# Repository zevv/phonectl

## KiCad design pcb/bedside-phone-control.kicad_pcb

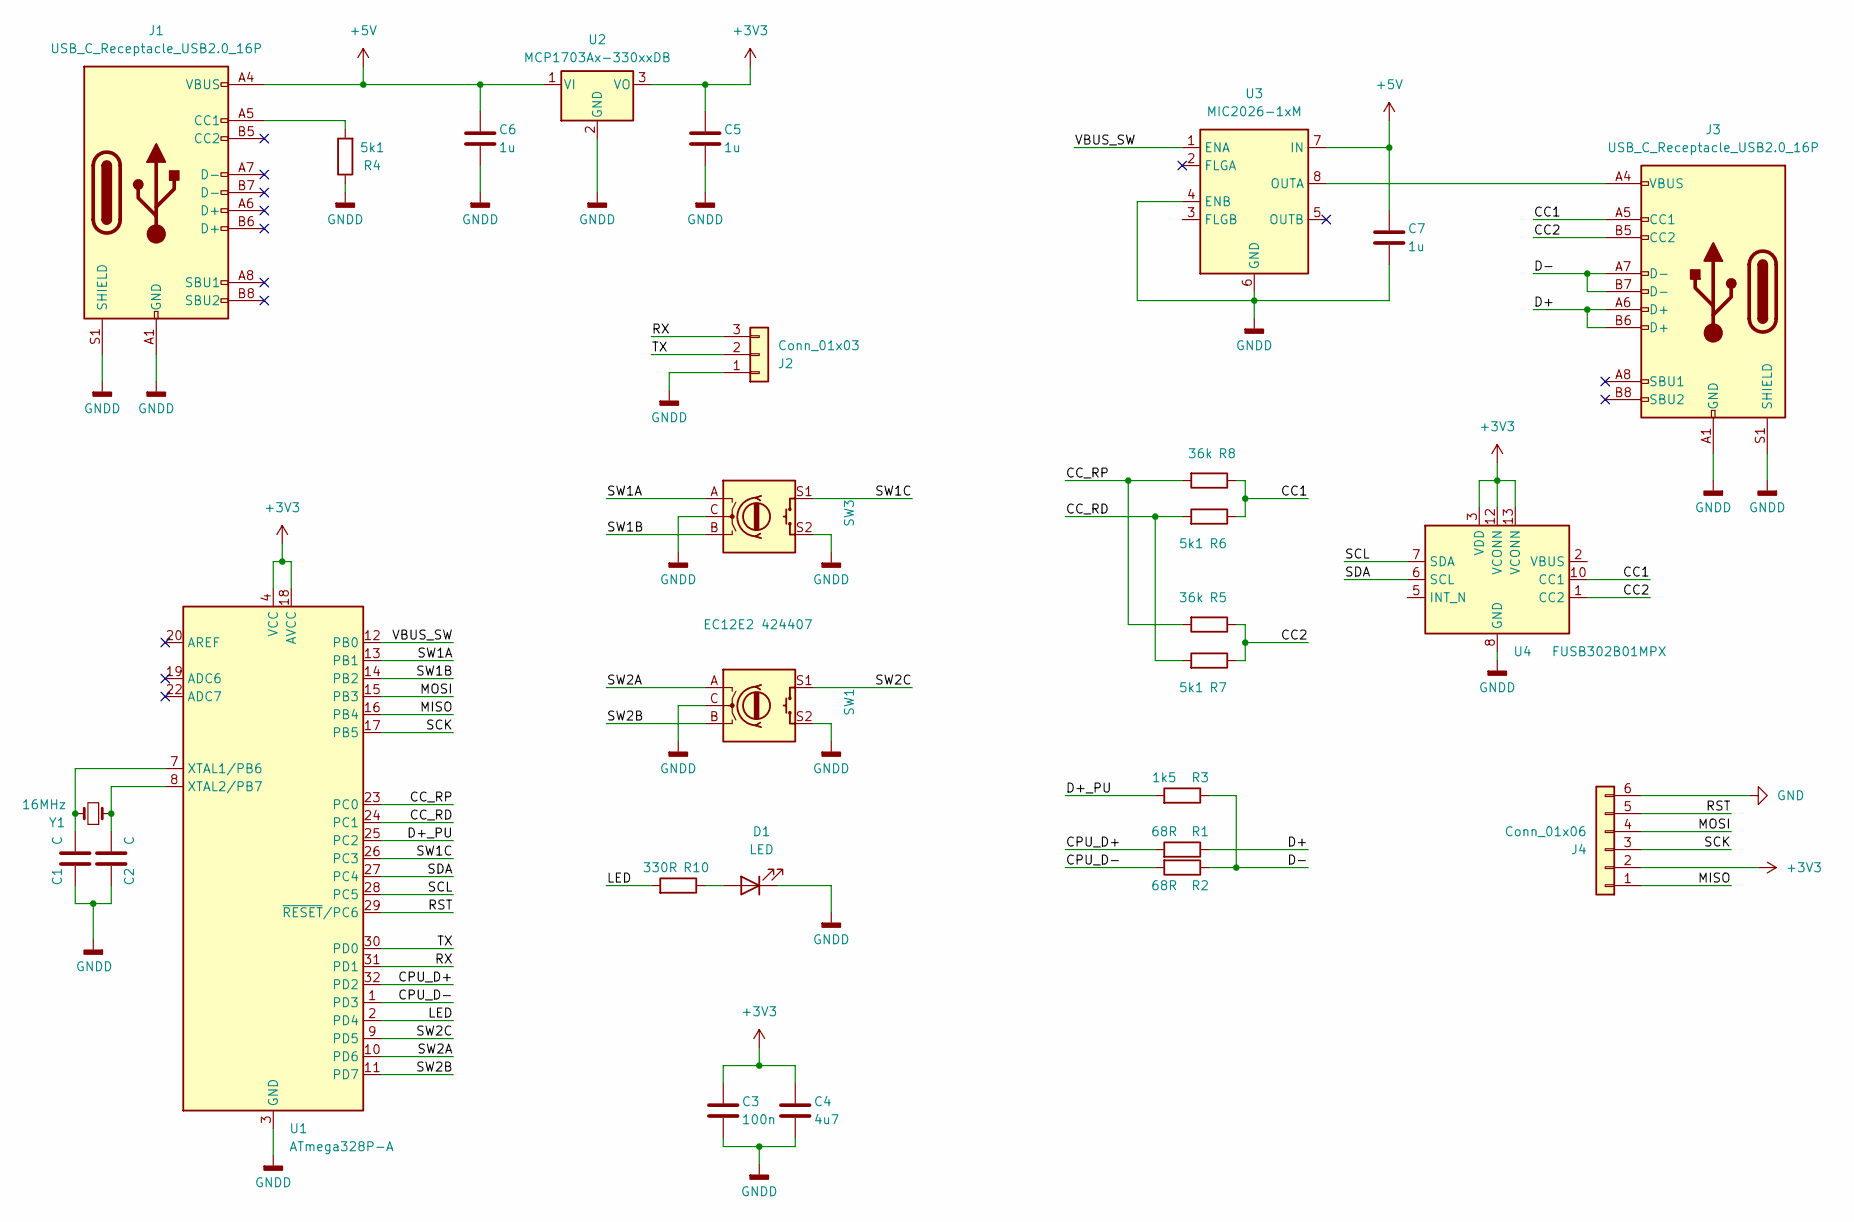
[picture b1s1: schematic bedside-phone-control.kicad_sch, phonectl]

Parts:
C1, C2: C; C_0603_1608Metric
C3: 100n; C_0603_1608Metric
C4: 4u7; C_0603_1608Metric
C5, C6, C7: 1u; C_0603_1608Metric
D1: LED; LED_D3.0mm
J1, J3: USB_C_Receptacle_USB2.0_16P; USB_C_Receptacle_Molex_105450-0101
J2: Conn_01x03; PinHeader_1x03_P2.54mm_Vertical
J4: Conn_01x06; PinHeader_2x03_P2.54mm_Vertical
R1, R2: 68R; R_0603_1608Metric
R3: 1k5; R_0603_1608Metric
R4, R6, R7: 5k1; R_0603_1608Metric
R5, R8: 36k; R_0603_1608Metric
R10: 330R; R_0603_1608Metric
SW1: RotaryEncoder_Switch; RotaryEncoder_Alps_EC11E-Switch_Vertical_H20mm
SW3: EC12E2 424407; RotaryEncoder_Alps_EC11E-Switch_Vertical_H20mm
U1: ATmega328P-A; TQFP-32_7x7mm_P0.8mm
U2: MCP1703Ax-330xxDB; SOT-223-3_TabPin2
U3: MIC2026-1xM; SOIC-8_3.9x4.9mm_P1.27mm
U4: FUSB302B01MPX; WQFN-14-1EP_2.5x2.5mm_P0.5mm_EP1.45x1.45mm
Y1: 16MHz; Crystal_SMD_Abracon_ABM3-2Pin_5.0x3.2mm_HandSoldering

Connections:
+3V3: C3.2, C4.2, C5.2, J4.2, U1.4 (VCC), U1.6 (VCC), U1.18 (AVCC), U2.3 (VO), U4.3 (VDD), U4.4 (VDD), U4.12 (VCONN), U4.13 (VCONN)
+5V: C6.2, C7.2, J1.A4 (VBUS), J1.A9 (VBUS), J1.B4 (VBUS), J1.B9 (VBUS), U2.1 (VI), U3.7 (IN)
/CC1: J3.A5 (CC1), R6.1, R8.1, U4.10 (CC1), U4.11 (CC1)
/CC2: J3.B5 (CC2), R5.1, R7.1, U4.1 (CC2), U4.14 (CC2)
/CC_RD: R6.2, R7.2, U1.24 (PC1)
/CC_RP: R5.2, R8.2, U1.23 (PC0)
/CPU_D+: R1.2, U1.32 (PD2)
/CPU_D-: R2.2, U1.1 (PD3)
/D+: J3.A6 (D+), J3.B6 (D+), R1.1
/D+_PU: R3.2, U1.25 (PC2)
/D-: J3.A7 (D-), J3.B7 (D-), R2.1, R3.1
/LED: R10.2, U1.2 (PD4)
/MISO: J4.1, U1.16 (PB4)
/MOSI: J4.4, U1.15 (PB3)
/RST: J4.5, U1.29 (~RESET/PC6)
/RX: J2.3, U1.31 (PD1)
/SCK: J4.3, U1.17 (PB5)
/SCL: U1.28 (PC5), U4.7 (SDA)
/SDA: U1.27 (PC4), U4.6 (SCL)
/SW1A: SW3.A, U1.13 (PB1)
/SW1B: SW3.B, U1.14 (PB2)
/SW1C: SW3.S1, U1.26 (PC3)
/SW2A: SW1.A, U1.10 (PD6)
/SW2B: SW1.B, U1.11 (PD7)
/SW2C: SW1.S1, U1.9 (PD5)
/TX: J2.2, U1.30 (PD0)
/VBUS_SW: U1.12 (PB0), U3.1 (ENA)
GND: J4.6
GNDD: C1.2, C2.2, C3.1, C4.1, C5.1, C6.1, C7.1, D1.1 (K), J1.A1 (GND), J1.A12 (GND), J1.B1 (GND), J1.B12 (GND), J1.S1 (SHIELD), J2.1, J3.A1 (GND), J3.A12 (GND), J3.B1 (GND), J3.B12 (GND), J3.S1 (SHIELD), R4.1, SW1.C, SW1.S2, SW3.C, SW3.S2, U1.3 (GND), U1.5 (GND), U1.21 (GND), U2.2 (GND), U3.4 (ENB), U3.6 (GND), U4.8 (GND), U4.9 (GND), U4.15 (GND)
unnamed: D1.2 (A), R10.1
unnamed: J1.A5 (CC1), R4.2
unnamed: C1.1, U1.7 (XTAL1/PB6), Y1.2
unnamed: C2.1, U1.8 (XTAL2/PB7), Y1.1
unnamed: J3.A4 (VBUS), J3.A9 (VBUS), J3.B4 (VBUS), J3.B9 (VBUS), U3.8 (OUTA)

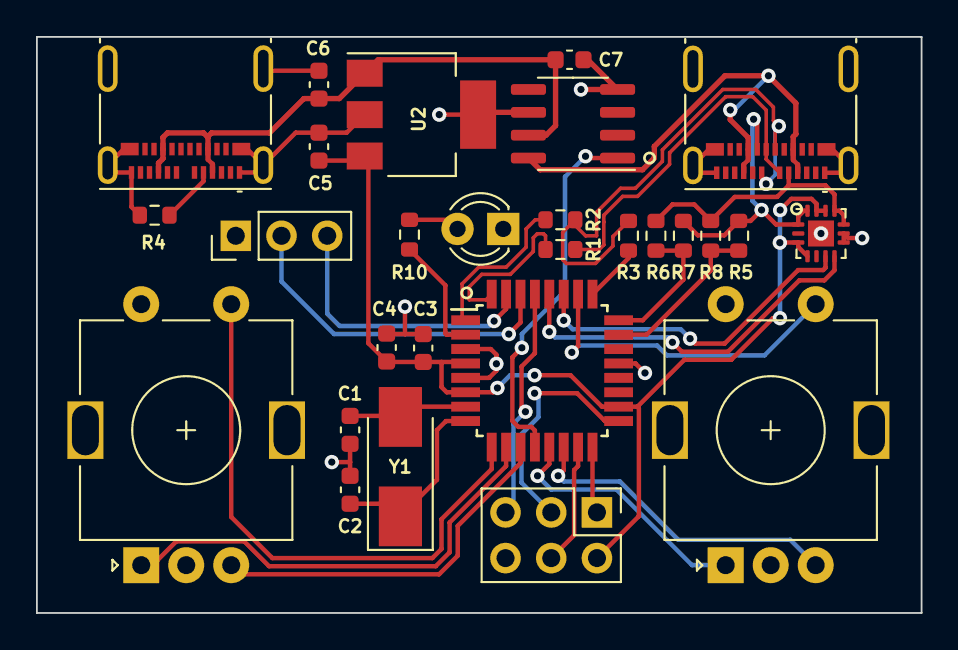
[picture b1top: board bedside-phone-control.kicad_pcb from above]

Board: 2 copper layers, 49.1 x 32.0 mm, 28 parts (0 on the bottom side), 33 nets.

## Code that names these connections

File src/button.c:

#include <avr/io.h>
#include <avr/interrupt.h>
#include <stdio.h>

#include "button.h"
#include "event.h"

#define R_START 0x0
#define R_CW_FINAL 0x1
#define R_CW_BEGIN 0x2
#define R_CW_NEXT 0x3
#define R_CCW_BEGIN 0x4
#define R_CCW_FINAL 0x5
#define R_CCW_NEXT 0x6

#define DIR_NONE 0x0
#define DIR_CW 0x10
#define DIR_CCW 0x20

const uint8_t ttable[7][4] = {
	{R_START,    R_CW_BEGIN,  R_CCW_BEGIN, R_START},
	{R_CW_NEXT,  R_START,     R_CW_FINAL,  R_START | DIR_CW},
	{R_CW_NEXT,  R_CW_BEGIN,  R_START,     R_START},
	{R_CW_NEXT,  R_CW_BEGIN,  R_CW_FINAL,  R_START},
	{R_CCW_NEXT, R_START,     R_CCW_BEGIN, R_START},
	{R_CCW_NEXT, R_CCW_FINAL, R_START,     R_START | DIR_CCW},
	{R_CCW_NEXT, R_CCW_FINAL, R_CCW_BEGIN, R_START},
};

static uint8_t state[2] = { R_START, R_START };


void button_init(void)
{
   // enable pullups
   PORTB |= (1<<PB1) | (1<<PB2);
   PORTC |= (1<<PC3);
   PORTD |= (1<<PD5) | (1<<PD6) | (1<<PD7);
   // enable pin change interrupt on PB1, PB2, PB6 and PB7
   PCMSK0 |= (1<<PCINT1) | (1<<PCINT2);
   PCMSK2 |= (1<<PCINT22) | (1<<PCINT23);
   PCICR |= (1<<PCIE0) | (1<<PCIE2);
}


static uint8_t process(uint8_t idx, uint8_t pinstate)
{
	state[idx] = ttable[state[idx] & 0xf][pinstate];
	return state[idx] & 0x30;
}


void button_poll(void)
{
    static uint16_t b1 = 0;
    static uint16_t b2 = 0;

    b1 = (b1 << 1) | !!(PINC & (1<<PC3));
    b2 = (b2 << 1) | !!(PIND & (1<<PD5));
        
    event_t ev;
    ev.type = EV_BUTTON;

    if(b1 == 0x8000) {
        ev.button.id = BUTTON_ID_R_PUSH;
        event_push(&ev);
    }

    if(b2 == 0x8000) {
        ev.button.id = BUTTON_ID_L_PUSH;
        event_push(&ev);
    }
}


ISR(PCINT0_vect)
{
	uint8_t b0 = !!(PINB & (1<<PB1));
	uint8_t b1 = !!(PINB & (1<<PB2));
	uint8_t dir = process(0, (b0 << 1) | (b1 << 0));
	if(dir != DIR_NONE) {
		event_t ev;
		ev.type = EV_BUTTON;
		ev.button.id = (dir == DIR_CW) ? BUTTON_ID_R_CW : BUTTON_ID_R_CCW;
		event_push(&ev);
	}
}


ISR(PCINT2_vect)
{
	uint8_t b0 = !!(PIND & (1<<PB6));
	uint8_t b1 = !!(PIND & (1<<PB7));
	uint8_t dir = process(1, (b0 << 1) | (b1 << 0));
	if(dir != DIR_NONE) {
		event_t ev;
		ev.type = EV_BUTTON;
		ev.button.id = (dir == DIR_CW) ? BUTTON_ID_L_CW : BUTTON_ID_L_CCW;
		event_push(&ev);
	}
}

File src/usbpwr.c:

#include <avr/io.h>
#include <stdio.h>
#include "usbpwr.h"

void usbpwr_init()
{
	DDRB |= (1 << PB0);
}


void usbpwr_enable_vbus(bool on)
{
	if (on) {
        printf("vbus on\n");
		PORTB |= (1 << PB0);
	} else {
        printf("vbus off\n");
		PORTB &= ~(1 << PB0);
	}
}


void usbpwr_set_cc(enum cc cc)
{
    DDRC &= ~((1 << PC0) | (1 << PC1));
    PORTC &= ~((1 << PC0) | (1 << PC1));

	switch(cc) {
        case CC_NONE:
            printf("cc none\n");
            break;
        case CC_PULLUP:
            printf("cc pullup\n");
            DDRC |= (1 << PC0);
            PORTC |= (1 << PC0);
            break;
        case CC_PULLDOWN:
            printf("cc pulldown\n");
            DDRC |= (1 << PC1);
            PORTC &= ~(1 << PC1);
            break;
    }
}


void usbpwr_connect(bool on)
{
    if(on) {
        printf("connect\n");
        DDRC |= (1 << PC2);
        PORTC |= (1 << PC2);
    } else {
        printf("disconnect\n");
        DDRC &= ~(1 << PC2);
        PORTC &= ~(1 << PC2);
    }
}

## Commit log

2024-02-28 checkin
2024-02-28 more checkin
2024-03-20 stuff
2024-03-21 getting there
2024-03-21 works
2024-03-21 done
2024-03-22 blend
